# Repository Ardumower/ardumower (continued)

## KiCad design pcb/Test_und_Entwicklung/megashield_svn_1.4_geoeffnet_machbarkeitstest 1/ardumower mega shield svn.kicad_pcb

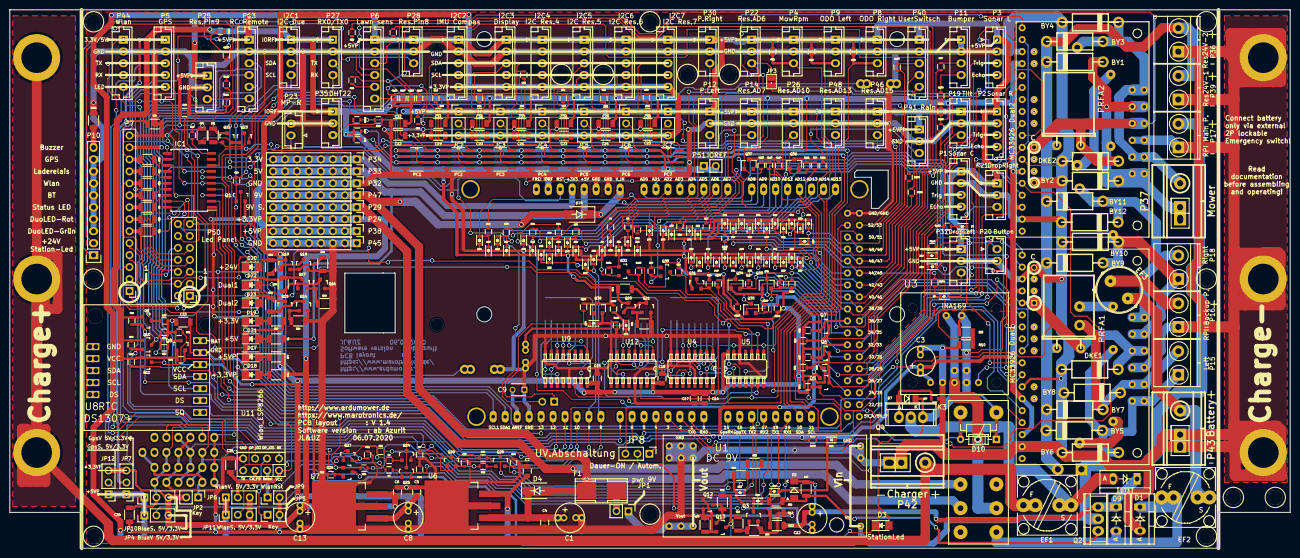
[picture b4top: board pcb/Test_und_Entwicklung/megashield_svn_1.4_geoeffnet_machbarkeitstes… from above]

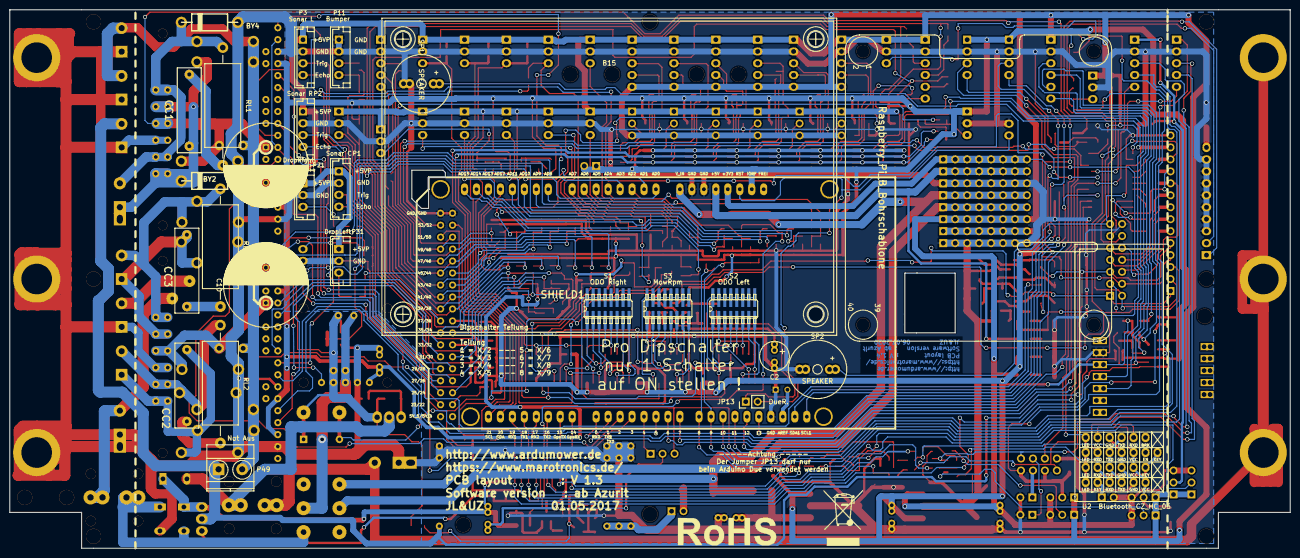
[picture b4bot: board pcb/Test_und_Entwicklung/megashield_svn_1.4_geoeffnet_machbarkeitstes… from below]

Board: 2 copper layers, 271.8 x 114.3 mm, 442 parts (21 on the bottom side), 281 nets.

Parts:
B1, B2, B3, B4, B5, B6, B7, B8, B17, B18, B19, B20, B21, B22: Bohrloch_3,2mm
B9, B10, B11, B12, B13, B14: Bohrloch_6,5mm
B15: BumperDuino_Bohrschablone
B16: Raspberry_Pi_B_Bohrschablone; Raspberry_Pi_B_Bohrschablone_Rueckseite
B23: Mülleimer; WEEE-Logo_8.4x12mm_SilkScreen
B24: Rohos; RoHS-Logo_6mm_SilkScreen
BY1, BY2, BY3, BY4, BY5, BY6, BY7, BY8, BY9, BY10, BY11, BY12: BY 500/1000; Diode_liegend_BY500_1000_RM15
C1, C8, C13: 22uF; Elko_vert_11.2x6.3mm_RM2.5_RM5.0
C2: 47uF; Elko_vert_11.2x6.3mm_RM2.5_RM5.0
C3: 10uF; Elko_vert_11.2x6.3mm_RM2.5_RM5.0
C4, C5, C6, C7, C14, C15, C16, C17, C18: 100nF; C_0805
C9: 100nF; C_Disc_D3_P2.5
C10, C11: 2200uF 63V; C_Radial_D18_L36_P7.5
C12: 22uF / 63V; Elko_vert_11.2x6.3mm_RM2.5_RM5.0
C19, C20, C21, C22, C23, C24, C25, C26, C27, C28, C29, C30, C31, C32, C33, C34, C35, C36: 100nF; C_1206
CC1, CC2, CC3: MP3-Y2 10N; Kondensator_cnp_18x5mm
D1, D9: MBR 1045; Diode_TO-220_Vertical
D2, D7: SMD ZF 15; MiniMELF_Standard
D3: StationLed; LED_1206
D4, D74: S 1G SMD; D_SMA_Standard
D5, D6, D8, D11, D12, D13, D14, D15, D16, D24, D25, D26, D27, D28, D29, D30, D31, D32, D33, D34, D35, D36, D37, D38, D39, D40, D41, D42, D43, D44, D45, D46, D47, D48, D49, D50, D51, D52, D53, D54, D55, D56, D57, D58, D59, D60, D61, D62, D63, D64, D65, D66, D67, D68, D69, D70, D71, D72, D75, D76: TSS0230LU; D_0603
D10: 1N4148; D_DO-35_SOD27_P7.62mm_Horizontal
D17: +5VP; LED_1206
D18: +3,3VP; LED_1206
D19: +3,3V; LED_1206
D20: +24V; LED_1206
D21: +5V; LED_1206
D22: Dual1; LED_1206
D23: Dual2; LED_1206
D73: MBR 1045; MBR1045
DKE1, DKE2: 15KE33CA; Diode_liegend_BY500_1000_RM15
Dual1, Dual2: MC33926; MC_33926_31polig_mit_Bohrloch_neue_Masse_mit_zweite_Lochrei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
EF1: F_5A; Fuseholder5x20_vert_closed_Bulgin_FX0456_und_TR15_Halter
EF2: F_10A; Fuseholder5x20_vert_closed_Bulgin_FX0456_und_TR15_Halter
EF3: 1A; Sicherungs_Sockel_für_TR5_TE5
F1: PTC; Fuse_SMD
I2C1: I2C Due; JST_EH_B04B-EH-A_04x2.50mm_Straight
I2C2: IMU Compas; JST_EH_B05B-EH-A_05x2.50mm_Straight
I2C3: Display; JST_EH_B05B-EH-A_05x2.50mm_Straight
I2C4: I2C Res.4; JST_EH_B05B-EH-A_05x2.50mm_Straight
I2C5: I2C Res.5; JST_EH_B05B-EH-A_05x2.50mm_Straight
I2C6: I2C Res.6; JST_EH_B05B-EH-A_05x2.50mm_Straight
I2C7: I2C Res.7; JST_EH_B05B-EH-A_05x2.50mm_Straight
IC1: UDN 2987 LWTR-6T; SOIC-20W_7.5x12.8mm_Pitch1.27mm
JC2, JC3, JC4, JC5, JC6, JC7: JUMPER3; Pin_Header_Straight_1x03_Pitch2.54mm
JP1: pwr 9V; Pin_Header_Straight_1x02_Pitch2.54mm
JP2, JP5: Key; Pin_Header_Straight_1x02_Pitch2.54mm
JP3: M1FB; SJ
JP4: BlueV 5V/3.3V; Pin_Header_Straight_1x03_Pitch2.54mm
JP6: WlanV. 5V/3.3V; Pin_Header_Straight_1x03_Pitch2.54mm
JP7: GpsV 5V/3.3V; Pin_Header_Straight_1x03_Pitch2.54mm
JP8: UV.Abschaltung; Pin_Header_Straight_1x03_Pitch2.54mm
JP9: WlanRst; Pin_Header_Straight_1x02_Pitch2.54mm
JP10: BlueS. 5V/3.3V; Pin_Header_Straight_1x03_Pitch2.54mm
JP11: WlanS. 5V/3.3V; Pin_Header_Straight_1x03_Pitch2.54mm
JP12: GpsS. 5V/3.3V; Pin_Header_Straight_1x03_Pitch2.54mm
JP13: DueR.; Pin_Header_Straight_1x02_Pitch2.54mm
K3: RELAY_2RT; Relais_DPDT_Schrack-RT2_RM5mm_3D_Kontaktbelegung_geändert_F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
P1: Sonar C; JST_EH_B04B-EH-A_04x2.50mm_Straight
P2: Sonar R; JST_EH_B04B-EH-A_04x2.50mm_Straight
P3: Sonar L; JST_EH_B04B-EH-A_04x2.50mm_Straight
P4: MowRpm; JST_EH_B03B-EH-A_03x2.50mm_Straight
P5: GPS; JST_EH_B05B-EH-A_05x2.50mm_Straight
P6: Lawn sens; JST_EH_B06B-EH-A_06x2.50mm_Straight
P7: Status LEDs; Socket_Strip_Straight_1x14_Pitch2.54mm
P8: ODO Right; JST_EH_B03B-EH-A_03x2.50mm_Straight
P9: ODO Left; JST_EH_B03B-EH-A_03x2.50mm_Straight
P10: Status LEDs GND; Socket_Strip_Straight_1x10_Led_Bargraph_Anzeige
P11: Bumper; JST_EH_B04B-EH-A_04x2.50mm_Straight
P12: P.Left; JST_EH_B03B-EH-A_03x2.50mm_Straight
P13: RC Remote; JST_EH_B06B-EH-A_06x2.50mm_Straight
P14: Res.AD7; JST_EH_B03B-EH-A_03x2.50mm_Straight
P15: Left; TerminalBlock_Pheonix_MKDS1.5-2pol
P16: RPI Backup P.; TerminalBlock_Pheonix_MKDS1.5-2pol
P17: RPI Main P.; TerminalBlock_Pheonix_MKDS1.5-2pol
P18: Right; TerminalBlock_Pheonix_MKDS1.5-2pol
P19: Tilt; JST_EH_B03B-EH-A_03x2.50mm_Straight
P20: Button; JST_EH_B02B-EH-A_02x2.50mm_Straight
P21: DropRight; JST_EH_B03B-EH-A_03x2.50mm_Straight
P22: Res.AD6; JST_EH_B03B-EH-A_03x2.50mm_Straight
P23: MP-R; JST_EH_B02B-EH-A_02x2.50mm_Straight
P24: +3.3VP; Pin_Header_Straight_1x08_Pitch2.54mm
P25: Res.Pin9; JST_EH_B03B-EH-A_03x2.50mm_Straight
P26: Res.AD10; JST_EH_B03B-EH-A_03x2.50mm_Straight
P27: RX0/TX0; JST_EH_B04B-EH-A_04x2.50mm_Straight
P28: Res.Pin8; JST_EH_B03B-EH-A_03x2.50mm_Straight
P29: 9V S.; Pin_Header_Straight_1x08_Pitch2.54mm
P30: P.Right; JST_EH_B03B-EH-A_03x2.50mm_Straight
P31: DropLeft; JST_EH_B03B-EH-A_03x2.50mm_Straight
P32, P45: GND; Pin_Header_Straight_1x08_Pitch2.54mm
P33: 5V; Pin_Header_Straight_1x08_Pitch2.54mm
P34: 3,3V; Pin_Header_Straight_1x08_Pitch2.54mm
P35: DHT22; JST_EH_B03B-EH-A_03x2.50mm_Straight
P36: Res24V-2; TerminalBlock_Pheonix_MKDS1.5-2pol
P37: Mower; Anschlussklemme_RM5,08-RM7,62
P38: +5VP; Pin_Header_Straight_1x08_Pitch2.54mm
P39: Res24V-1; TerminalBlock_Pheonix_MKDS1.5-2pol
P40: UserSwitsch; JST_EH_B05B-EH-A_05x2.50mm_Straight
P41: Rain; JST_EH_B03B-EH-A_03x2.50mm_Straight
P42: Charger; Anschlussklemme_RM5,08-RM7,62
P43: Battery; Anschlussklemme_RM5,08-RM7,62
P44: Wlan; JST_EH_B05B-EH-A_05x2.50mm_Straight
P46: Res.AD15; JST_EH_B03B-EH-A_03x2.50mm_Straight
P47: 9V; Pin_Header_Straight_1x08_Pitch2.54mm
P48: Res.AD13; JST_EH_B03B-EH-A_03x2.50mm_Straight
P49: Not Aus; TerminalBlock_Pheonix_MKDS1.5-2pol
P50: Led Panel; Pin_Header_Straight_2x07_Pitch2.54mm
P51: IOREF; Socket_Strip_Straight_1x02_Pitch2.54mm
PC1, PC2, PC3, PC4, PC5, PC6, PC7: PCA9517D; SOIC127P600X175-8N
PRFA1, PRFA2: PFRA 500; PRFA_500
Q1, Q24, Q25, Q26, Q27, Q28, Q29, Q38: BC847B; SOT-23
Q2, Q4: IRF9540N; TO-220
Q3, Q12, Q13, Q14, Q15, Q16, Q17, Q18, Q19, Q20, Q21, Q22, Q23: BC817; SOT-23
Q5, Q6, Q7, Q8, Q9, Q10, Q11, Q30, Q31, Q32, Q33, Q34, Q35, Q36, Q37: BSS138; SOT-23
R1, R2, R5, R17, R20, R21, R22, R25, R77, R134: 220R; R_1206
R3, R4, R26, R27, R29, R50, R54, R82, R83, R84, R85, R86, R87, R88, R89, R90, R103, R104, R105, R106, R107, R108, R109, R110, R111, R112: 300R; R_0603
R6, R7, R16, R28, R30, R31, R92, R93, R96: 4K7; R_0603
R8, R14, R15, R39, R42, R46, R49, R51, R52, R53, R55, R56, R58, R59, R60, R61, R62, R63, R64, R65, R66, R67, R68, R69, R70, R71, R91, R94, R95, R97, R98, R99, R100, R101, R102, R113, R114, R115, R116, R117, R118, R119, R120, R121, R122, R123, R124, R131, R132, R133, R137: 10K; R_0603
R9, R12: 100K 0,1%; R_1206
R10, R13: 10K 0,1%; R_1206
R11, R73, R79: 68R; R_1206
R18, R43: 2k2; R_0603
R19, R38, R72, R74, R76, R81: 8K2; R_1206
R23, R33, R78: 100R; R_1206
R24, R75, R80: 180R; R_1206
R32: 1K; R_1206
R34, R35: 10K; R_1206
R36: 30K; R_1206
R37: 100K; R_1206
R40, R41, R44, R45, R47, R48, R125, R126, R127, R128, R129, R130: XXXX; R_0603
R57: 100K; R_0603
R135: 56K; R_0603
R136: 1K; R_0603
RL1, RL2, RL3: 1,8R 2W METALL; Resistor_Horizontal_RM25mm-2W
S1: ODO Right; SW_DIP_x8_SMD
S2: ODO Left; SW_DIP_x8_SMD
S3: MowRpm; SW_DIP_x8_SMD
SHIELD1: ARDUINO_MEGA_SHIELD; ARDUINO_MEGA_SHIELD_DUO_3D
SP1, SP2: SPEAKER; Buzzer_12x9.5RM7.6_RM5.0
U1: DC 9V; DC_DC_DSN2596_mit_Bohrloch_doppelte_Lochreihe
U2: Bluetooth_CZ_HC_05; Bluetooth_Buchse_Platz_mit_Beschriftung_4_fach
U3: INA169
U4, U9, U12: 4017; 40xx-SO16
U5: 4081; 40xx-SO14
U6: LM2940CS-5.0; TO-263-3Lead
U7: LM3940IS-3.3; TO-263-3Lead
U8: DS1307+; Tiny_RTC_DS1307_geändert_mit_Bohrloch_4Lochreihen
U11: Wlan_ESP8266; Wlan_ESP8266_3D_mit_Pin_Beschreibung_ohne_Rahmen

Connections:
9Vgeschaltet: K3.3 (R1), P29.1, P29.2, P29.3, P29.4, P29.5, P29.6, P29.7, P29.8
+3.3VP: C6.1, C13.1, I2C2.5, I2C3.5, I2C4.5, I2C5.5, I2C6.5, I2C7.5, JC2.3, JC3.3, JC4.3, JC5.3, JC6.3, JC7.3, JP2.2, JP4.3, JP6.3, JP7.3, JP10.3, JP11.3, JP12.3, P24.1, P24.2, P24.3, P24.4, P24.5, P24.6, P24.7, P24.8, R78.1, U7.3 (OUT)
+3V3: P34.1, P34.2, P34.3, P34.4, P34.5, P34.6, P34.7, P34.8, R23.1, SHIELD1.3V3
+5V: P33.1, P33.2, P33.3, P33.4, P33.5, P33.6, P33.7, P33.8, R1.1, SHIELD1.5V
+5VP: C5.1, C7.1, C8.1, C14.1, C15.1, C16.1, C17.1, C18.1, C22.1, C33.1, I2C2.1, I2C3.1, I2C4.1, I2C5.1, I2C6.1, I2C7.1, IC1.11 (VS), JC2.1, JC3.1, JC4.1, JC5.1, JC6.1, JC7.1, JP4.1, JP6.1, JP7.1, JP10.1, JP11.1, JP12.1, P1.1, P2.1, P3.1, P4.1, P6.1, P8.1, P9.1, P12.1, P13.1, P14.1, P19.1, P21.1, P22.1, P25.1, P26.1, P28.1, P30.1, P31.1, P38.1, P38.2, P38.3, P38.4, P38.5, P38.6, P38.7, P38.8, P40.1, P41.1, P46.1, P48.1, PC1.8 (VCCB), R28.2, R30.2, R31.1, R43.1, R59.1, R61.1, R63.1, R65.1, R67.1, R69.1, R71.1, R77.1, R98.1, R100.1, R102.1, R116.1, R118.1, R120.1, R122.1, R124.1, U4.16 (VDD), U5.14 (Vdd), U6.3 (OUT), U7.1 (IN), U8.3 (VCC), U9.16 (VDD), U12.16 (VDD)
+9V: D4.2 (A), D74.2 (A), F1.2, K3.5 (C1), P47.1, P47.2, P47.3, P47.4, P47.5, P47.6, P47.7, P47.8
+24V: D20.2 (A), P7.5, P17.2, P49.1, P50.5, Q2.2 (D), U1.3 (VIN)
/+24V: BY1.1 (K), BY3.1 (K), BY5.1 (K), BY7.1 (K), BY9.1 (K), BY11.1 (K), P36.2, P39.2, P49.2, PRFA1.1, PRFA2.1
/Anschlußstecker/5V_IN: P19.3, Q37.3 (D), R124.2
/Anschlußstecker/5V_IN_1: P1.4, Q5.3 (D), R59.2
/Anschlußstecker/5V_IN_2: P2.4, Q6.3 (D), R61.2
/Anschlußstecker/5V_IN_3: P2.3, Q34.3 (D), R118.2
/Anschlußstecker/5V_IN_4: P41.3, Q36.3 (D), R122.2
/Anschlußstecker/5V_IN_5: P3.4, Q7.3 (D), R63.2
/Anschlußstecker/5V_IN_6: P3.3, Q33.3 (D), R116.2
/Anschlußstecker/5V_IN_7: P1.3, Q35.3 (D), R120.2
/Anschlußstecker/5V_IN_8: P13.6, Q11.3 (D), R71.2
/Anschlußstecker/5V_IN_9: P13.5, Q10.3 (D), R69.2
/Anschlußstecker/5V_IN_10: P13.4, Q9.3 (D), R67.2
/Anschlußstecker/5V_IN_11: P13.3, Q8.3 (D), R65.2
/Anschlußstecker/Ausgang1: Q32.3 (D), R102.2, U5.3
/Anschlußstecker/Ausgang2: Q31.3 (D), R100.2, U5.4
/Anschlußstecker/Ausgang3: Q30.3 (D), R98.2, U5.10
/Anschlußstecker/Eingang1: P8.3, R28.1, U4.14 (CP0), U5.1
/Anschlußstecker/Eingang2: P9.3, R30.1, U5.5, U9.14 (CP0)
/Anschlußstecker/Eingang3: P4.3, R31.2, U5.8, U12.14 (CP0)
/Batterieeingang 24V: C12.1, D2.1 (K), D9.1 (K), D73.1 (K), Q2.3 (S), R12.1, R37.1
/Eingang: D73.2 (A), EF1.2, Q4.2 (D)
/Motortreiber/MotorOUT1: BY9.2 (A), BY10.1 (K), CC3.1, Dual1.23 (M2OUT1), P18.1
/Motortreiber/MotorOUT1_1: BY5.2 (A), BY6.1 (K), CC2.1, Dual1.19 (M1OUT1), P15.1
/Motortreiber/MotorOUT1_2: BY1.2 (A), BY2.1 (K), CC1.1, Dual2.19 (M1OUT1), Dual2.23 (M2OUT1), P37.1
/Motortreiber/MotorOUT2: BY3.2 (A), BY4.1 (K), Dual2.20 (M1OUT2), Dual2.24 (M2OUT2), P37.2, RL1.2
/Motortreiber/MotorOUT2_1: BY7.2 (A), BY8.1 (K), Dual1.20 (M1OUT2), P15.2, RL2.2
/Motortreiber/MotorOUT2_2: BY11.2 (A), BY12.1 (K), Dual1.24 (M2OUT2), P18.2, RL3.2
Charg_Pin_+: B9.1 (B3,2), B10.1 (B3,2), B11.1 (B3,2), EF1.1, P42.2
DHT22: P35.3, R39.2, R109.1
DropLeft: D5.1 (K), P31.3
DropRight: D6.1 (K), P21.3
Dual1: C10.1, D22.2 (A), DKE1.1 (K), Dual1.22 (VIN), PRFA1.2
Dual2: C11.1, D23.2 (A), DKE2.1 (K), Dual2.22 (VIN), PRFA2.2
DuoLED-Rot: IC1.2 (IN2), SHIELD1.7
DuoLED_Grün: IC1.1 (IN1), SHIELD1.6
GND: B12.1 (B3,2), B13.1 (B3,2), B14.1 (B3,2), BY2.2 (A), BY4.2 (A), BY6.2 (A), BY8.2 (A), BY10.2 (A), BY12.2 (A), C1.2, C2.2, C3.2, C4.2, C5.2, C6.2, C7.2, C8.2, C9.1, C10.2, C11.2, C13.2, C14.2, C15.2, C16.2, C17.2, C18.2, C19.2, C20.2, C21.2, C22.2, C23.2, C24.2, C25.2, C26.2, C27.2, C28.2, C29.2, C30.2, C31.2, C32.2, C33.2, C34.2, C35.2, C36.2, D1.2 (A), D16.2 (A), D17.1 (K), D18.1 (K), D19.1 (K), D21.1 (K), D24.2 (A), D25.2 (A), D27.2 (A), D30.2 (A), D34.2 (A), D35.2 (A), D36.2 (A), D38.2 (A), D40.2 (A), D42.2 (A), D44.2 (A), D46.2 (A), D48.2 (A), D50.2 (A), D52.2 (A), D54.2 (A), D56.2 (A), D58.2 (A), D60.2 (A), D62.2 (A), D64.2 (A), D66.2 (A), D68.2 (A), D70.2 (A), D72.2 (A), D75.2 (A), DKE1.2 (A), DKE2.2 (A), Dual1.2 (GND), Dual1.7 (M1D1), Dual1.16 (M2D1), Dual1.21 (GND), Dual2.2 (GND), Dual2.7 (M1D1), Dual2.16 (M2D1), Dual2.21 (GND), I2C1.2, I2C2.2, I2C3.2, I2C4.2, I2C5.2, I2C6.2, I2C7.2, IC1.12 (GND), JP5.2, JP9.2, P1.2, P2.2, P3.2, P4.2, P5.2, P6.2, P7.14, P8.2, P9.2, P10.3, P10.4, P10.5, P10.6, P10.7, P10.8, P10.9, P11.1, P11.2, P12.2, P13.2, P14.2, P16.1, P17.1, P19.2, P20.2, P21.2, P22.2, P23.2, P25.2, P26.2, P27.2, P28.2, P30.2, P31.2, P32.1, P32.2, P32.3, P32.4, P32.5, P32.6, P32.7, P32.8, P35.2, P36.1, P39.1, P40.2, P41.2, P42.1, P43.1, P44.2, P45.1, P45.2, P45.3, P45.4, P45.5, P45.6, P45.7, P45.8, P46.2, P48.2, P50.14, PC1.4 (GND), PC2.4 (GND), PC3.4 (GND), PC4.4 (GND), PC5.4 (GND), PC6.4 (GND), PC7.4 (GND), Q1.2 (E), Q3.2 (E), Q12.2 (E), Q14.2 (E), Q16.2 (E), Q18.2 (E), Q21.2 (E), Q23.2 (E), R8.2, R10.2, R11.2, R13.2, R14.2, R15.2, R24.2, R35.2, R57.2, R73.2, R75.2, R79.2, R80.2, R91.2, R94.2, R95.2, R134.2, R136.2, SHIELD1.GND1, SHIELD1.GND2, SHIELD1.GND3, SHIELD1.GND4, SHIELD1.GND5, SP1.1, SP2.1, U1.1 (GND), U1.4 (GND), U2.GND, U3.2 (GND), U4.8 (VSS), U4.13 (~CP1), U5.7 (Vss), U5.12, U5.13, U6.2 (GND_2), U6.4 (GND), U7.2 (GND_2), U7.4 (GND), U8.2 (GND), U9.8 (VSS), U9.13 (~CP1), U11.GND, U12.8 (VSS), U12.13 (~CP1)
GPS-LED: IC1.7 (IN7), P5.5
GPS_RX: Q28.2 (E), R94.1, SHIELD1.15 (RX3)
GPS_TX: R96.2, SHIELD1.14 (TX3)
IOREF: C3.1, C26.1, C27.1, C28.1, C29.1, C30.1, C31.1, C32.1, D8.1 (K), D11.1 (K), D26.1 (K), D28.1 (K), D29.1 (K), D31.1 (K), D32.1 (K), D33.1 (K), D37.1 (K), D39.1 (K), D41.1 (K), D43.1 (K), D45.1 (K), D47.1 (K), D49.1 (K), D51.1 (K), D53.1 (K), D55.1 (K), D57.1 (K), D59.1 (K), D61.1 (K), D63.1 (K), D65.1 (K), D67.1 (K), D69.1 (K), D71.1 (K), Dual1.3 (Vdd), Dual1.6 (M1nD2), Dual1.15 (M2nD2), Dual2.3 (Vdd), Dual2.6 (M1nD2), Dual2.15 (M2nD2), I2C1.1, JP8.3, P27.1, P35.1, P51.1, P51.2, PC1.1 (VCCA), PC2.1 (VCCA), PC3.1 (VCCA), PC4.1 (VCCA), PC5.1 (VCCA), PC6.1 (VCCA), PC7.1 (VCCA), Q5.1 (G), Q6.1 (G), Q7.1 (G), Q8.1 (G), Q9.1 (G), Q10.1 (G), Q11.1 (G), Q24.3 (C), Q25.3 (C), Q28.3 (C), Q30.1 (G), Q31.1 (G), Q32.1 (G), Q33.1 (G), Q34.1 (G), Q35.1 (G), Q36.1 (G), Q37.1 (G), Q38.3 (C), R39.1, R47.1, R48.1, R58.1, R60.1, R62.1, R64.1, R66.1, R68.1, R70.1, R97.1, R99.1, R101.1, R113.2, R114.2, R115.1, R117.1, R119.1, R121.1, R123.1, R125.2, R126.2, R127.2, R128.2, R129.2, R130.2, R131.2, R132.2, R133.2, R135.1, R137.2, SHIELD1.IORE (IOREF), U3.1 (VCC)
Led-BT: IC1.4 (IN4), U2.LED
Led-Status: IC1.3 (IN3), SHIELD1.13
Led-Wlan: IC1.5 (IN5), P44.5, U11.GP_2 (GP_IO2)
unnamed: C1.1, C4.1, D4.1 (K), U6.1 (IN)
unnamed: C2.1, D75.1 (K), Q38.1 (B), R135.2
unnamed: C9.2, SHIELD1.AREF
unnamed: C12.2, D12.2 (A), R34.1
unnamed: C19.1, JC2.2, PC2.8 (VCCB), R40.1, R44.1
unnamed: C20.1, JC3.2, PC3.8 (VCCB), R41.1, R45.1
unnamed: C21.1, JC4.2, PC4.8 (VCCB), R42.1, R46.1
unnamed: C23.1, JC5.2, PC5.8 (VCCB), R51.1, R55.1
unnamed: C24.1, JC6.2, PC6.8 (VCCB), R52.1, R56.1
unnamed: C25.1, JC7.2, PC7.8 (VCCB), R49.1, R53.1
unnamed: C34.1, JP4.2, U2.VCC
unnamed: C35.1, JP6.2, P44.1, U11.CH_P (CH_PD), U11.VCC
unnamed: C36.1, JP7.2, P5.1
unnamed: CC1.2, RL1.1
unnamed: CC2.2, RL2.1
unnamed: CC3.2, RL3.1
unnamed: D1.1 (K), D9.2 (A), EF2.1, K3.16 (T2)
unnamed: D2.2 (A), Q2.1 (G), R32.2, R37.2
unnamed: D3.1 (K), Q13.3 (C), R72.1
unnamed: D5.2 (A), R104.1
unnamed: D6.2 (A), R103.1
unnamed: D7.2 (A), Q4.1 (G), R57.1
unnamed: D10.2 (A), K3.9, Q1.3 (C)
unnamed: D11.2 (A), D24.1 (K), R3.2, SHIELD1.AD5
unnamed: D12.1 (K), R33.1, R34.2
unnamed: D13.2 (A), D15.2 (A), R32.1, R33.2
unnamed: D15.1 (K), Q3.3 (C)
unnamed: D8.2 (A), D16.1 (K), R4.2, SHIELD1.AD4
unnamed: D17.2 (A), R77.2
unnamed: D18.2 (A), R78.2
unnamed: D19.2 (A), R23.2
unnamed: D20.1 (K), Q19.3 (C), R76.1
unnamed: D21.2 (A), R1.2
unnamed: D22.1 (K), Q17.3 (C), R38.1
unnamed: D23.1 (K), Q15.3 (C), R19.1
unnamed: D25.1 (K), D26.2 (A), R103.2, R114.1, SHIELD1.23 (PA1)
unnamed: D27.1 (K), D28.2 (A), R110.2, SHIELD1.35 (PC2)
unnamed: D29.2 (A), D30.1 (K), R87.2, R132.1, SHIELD1.38 (PD7)
unnamed: D31.2 (A), D34.1 (K), R105.2, R131.1, SHIELD1.39 (PG2)
unnamed: D32.2 (A), D35.1 (K), R111.2, R129.1, SHIELD1.9
unnamed: D33.2 (A), D36.1 (K), R112.2, R130.1, SHIELD1.8
unnamed: D37.2 (A), D38.1 (K), R29.2, R126.1, SHIELD1.40 (PG1)
unnamed: D39.2 (A), D40.1 (K), R54.2, R125.1, SHIELD1.41 (PG0)
unnamed: D41.2 (A), D42.1 (K), R83.2, R128.1, SHIELD1.42 (PL7)
unnamed: D43.2 (A), D44.1 (K), R85.2, R127.1, SHIELD1.43 (PL6)
unnamed: D45.2 (A), D46.1 (K), R86.2, SHIELD1.44 (PL5)
unnamed: D47.2 (A), D48.1 (K), R104.2, R113.1, SHIELD1.45 (PL4)
unnamed: D49.2 (A), D50.1 (K), R108.2, SHIELD1.47 (PL2)
unnamed: D51.2 (A), D52.1 (K), R106.2, SHIELD1.46 (PL3)
unnamed: D53.2 (A), D54.1 (K), R26.2, SHIELD1.AD7
unnamed: D55.2 (A), D56.1 (K), R82.2, SHIELD1.AD6
unnamed: D57.2 (A), D58.1 (K), R109.2, SHIELD1.49 (PL0)
unnamed: D59.2 (A), D60.1 (K), R84.2, SHIELD1.AD2
unnamed: D61.2 (A), D62.1 (K), R107.2, SHIELD1.48 (PL1)
unnamed: D63.2 (A), D64.1 (K), R90.2, SHIELD1.AD8
unnamed: D65.2 (A), D66.1 (K), R27.2, SHIELD1.AD15
unnamed: D67.2 (A), D68.1 (K), R89.2, SHIELD1.AD9
unnamed: D69.2 (A), D70.1 (K), R50.2, SHIELD1.AD13
unnamed: D71.2 (A), D72.1 (K), R88.2, SHIELD1.AD10
unnamed: D74.1 (K), SHIELD1.V_IN
unnamed: D76.1 (K), Q38.2 (E), R136.1
unnamed: D76.2 (A), JP13.1, R137.1
unnamed: Dual2.9 (M1FB), JP3.2
unnamed: EF2.2, EF3.1, P43.2
unnamed: EF3.2, P16.2
unnamed: F1.1, JP1.2
unnamed: IC1.10 (OE/~R), R43.2
unnamed: IC1.13 (OUT8), P7.13, P50.13, SP1.2, SP2.2
unnamed: IC1.14 (OUT7), R25.1
unnamed: IC1.15 (OUT6), R17.1
unnamed: IC1.16 (OUT5), R22.1
unnamed: IC1.17 (OUT4), R2.1
unnamed: IC1.18 (OUT3), R5.1
unnamed: IC1.19 (OUT2), R20.1
unnamed: IC1.20 (OUT1), R21.1
unnamed: JP1.1, U1.2 (Vout)
unnamed: JP2.1, U2.Key
unnamed: JP5.1, U11.GP_0 (GP_IO0)
unnamed: JP8.2, R36.2
unnamed: JP9.1, U11.Rese (Reset)
unnamed: JP10.2, Q26.3 (C)
unnamed: JP11.2, Q27.3 (C)
unnamed: JP12.2, Q29.3 (C)
unnamed: K3.12 (C2), U3.5 (IP-)
unnamed: P5.3, R93.2
unnamed: P5.4, Q29.2 (E), R95.1
unnamed: P7.2, P10.1, P50.2, Q22.3 (C), R81.1
unnamed: P7.3, P10.2, P50.3, Q20.3 (C), R74.1
unnamed: P10.10, R134.1
unnamed: P44.3, R7.2, U11.TX
unnamed: P44.4, Q27.2 (E), R91.1, U11.RX
unnamed: P7.6, P50.6, R21.2
unnamed: P7.7, P50.7, R20.2
unnamed: P7.8, P50.8, R5.2
unnamed: P7.9, P50.9, R2.2
unnamed: P7.10, P50.10, R22.2
unnamed: P7.11, P50.11, R17.2
unnamed: P7.12, P50.12, R25.2
unnamed: Q1.1 (B), R18.2
unnamed: Q3.1 (B), R35.1, R36.1
unnamed: Q12.1 (B), Q13.2 (E), R73.1
unnamed: Q12.3 (C), Q13.1 (B), R72.2
unnamed: Q14.1 (B), Q15.2 (E), R24.1
unnamed: Q14.3 (C), Q15.1 (B), R19.2
unnamed: Q16.1 (B), Q17.2 (E), R75.1
unnamed: Q16.3 (C), Q17.1 (B), R38.2
unnamed: Q18.1 (B), Q19.2 (E), R80.1
unnamed: Q18.3 (C), Q19.1 (B), R76.2
unnamed: Q20.1 (B), Q21.3 (C), R74.2
unnamed: Q20.2 (E), Q21.1 (B), R11.1
unnamed: Q22.1 (B), Q23.3 (C), R81.2
unnamed: Q22.2 (E), Q23.1 (B), R79.1
unnamed: Q24.1 (B), R6.1
unnamed: Q25.1 (B), R7.1
unnamed: Q26.1 (B), R16.1
unnamed: Q26.2 (E), R15.1, U2.RXD
unnamed: Q27.1 (B), R92.1
unnamed: Q28.1 (B), R93.1
unnamed: Q29.1 (B), R96.1
unnamed: R6.2, U2.TXD
unnamed: S1.1, U4.4 (Q2)
unnamed: S1.2, U4.7 (Q3)
unnamed: S1.3, U4.10 (Q4)
unnamed: S1.4, U4.1 (Q5)
unnamed: S1.5, U4.5 (Q6)
unnamed: S1.6, U4.6 (Q7)
unnamed: S1.7, U4.9 (Q8)
unnamed: S1.8, U4.11 (Q9)
unnamed: S1.9, S1.10, S1.11, S1.12, S1.13, S1.14, S1.15, S1.16, U4.15 (MR)
unnamed: S2.1, U9.4 (Q2)
unnamed: S2.2, U9.7 (Q3)
unnamed: S2.3, U9.10 (Q4)
unnamed: S2.4, U9.1 (Q5)
unnamed: S2.5, U9.5 (Q6)
unnamed: S2.6, U9.6 (Q7)
unnamed: S2.7, U9.9 (Q8)
unnamed: S2.8, U9.11 (Q9)
unnamed: S2.9, S2.10, S2.11, S2.12, S2.13, S2.14, S2.15, S2.16, U9.15 (MR)
unnamed: S3.1, U12.4 (Q2)
unnamed: S3.2, U12.7 (Q3)
unnamed: S3.3, U12.10 (Q4)
unnamed: S3.4, U12.1 (Q5)
unnamed: S3.5, U12.5 (Q6)
unnamed: S3.6, U12.6 (Q7)
unnamed: S3.7, U12.9 (Q8)
unnamed: S3.8, U12.11 (Q9)
unnamed: S3.9, S3.10, S3.11, S3.12, S3.13, S3.14, S3.15, S3.16, U12.15 (MR)
unnamed: U4.2 (Q1), U5.2
unnamed: U5.6, U9.2 (Q1)
unnamed: U5.9, U12.2 (Q1)
RX0: P27.3, SHIELD1.0 (RX0)
RX1: Q25.2 (E), R14.1, SHIELD1.19 (RX1)
RX2: Q24.2 (E), R8.1, SHIELD1.17 (RX2)
RelaisAbschaltung: JP8.1, SHIELD1.4
ReserveAD6: JP3.1, P22.3, R82.1
ReserveAD7: P14.3, R26.1
ReserveAD10: P26.3, R88.1
ReservePin8: P28.3, R112.1
ReservePin9: P25.3, R111.1
Reset: JP13.2, P23.1, SHIELD1.RST
Resv.PinAD13: P48.3, R50.1
Resv.PinAD15: P46.3, R27.1
SCL: PC1.2 (SCLA), PC2.2 (SCLA), PC3.2 (SCLA), PC4.2 (SCLA), PC5.2 (SCLA), PC6.2 (SCLA), PC7.2 (SCLA), R48.2, SHIELD1.21 (SCL)
SCL1: PC1.7 (SCLB), U8.5 (SCL)
SCL2: I2C2.4, PC2.7 (SCLB), R44.2
SCL3: I2C3.4, PC3.7 (SCLB), R45.2
SCL4: I2C4.4, PC4.7 (SCLB), R46.2
SCL5: I2C5.4, PC5.7 (SCLB), R51.2
SCL6: I2C6.4, PC6.7 (SCLB), R52.2
SCL7: I2C7.4, PC7.7 (SCLB), R49.2
SCL22: I2C1.4, SHIELD1.SCL1
SDA: PC1.3 (SDAA), PC2.3 (SDAA), PC3.3 (SDAA), PC4.3 (SDAA), PC5.3 (SDAA), PC6.3 (SDAA), PC7.3 (SDAA), R47.2, SHIELD1.20 (SDA)
SDA1: PC1.6 (SDAB), U8.4 (SDA)
SDA2: I2C2.3, PC2.6 (SDAB), R40.2
SDA3: I2C3.3, PC3.6 (SDAB), R41.2
SDA4: I2C4.3, PC4.6 (SDAB), R42.2
SDA5: I2C5.3, PC5.6 (SDAB), R55.2
SDA6: I2C6.3, PC6.6 (SDAB), R56.2
SDA7: I2C7.3, PC7.6 (SDAB), R53.2
SDA22: I2C1.3, SHIELD1.SDA1
StationLed: D3.2 (A), D7.1 (K), D10.1 (K), K3.8, P7.4, P50.4, Q4.3 (S), R9.1, U3.4 (IP+)
TX0: P27.4, SHIELD1.1 (TX0)
TX1: R92.2, SHIELD1.18 (TX1)
TX2: R16.2, SHIELD1.16 (TX2)
Taster: D13.1 (K), D14.1 (K), P7.1, P20.1, P50.1
pinBatteryVoltage: R12.2, R13.1, R84.1
pinBumperLeft: P11.4, R105.1
pinBumperRight: P11.3, R87.1
pinButton: D14.2 (A), R133.1, SHIELD1.51 (PB2_(MOSI))
pinBuzzer: IC1.8 (IN8), SHIELD1.53 (PB0_(SS))
pinChargeCurrent: R90.1, U3.3 (OUT)
pinChargeVoltage: R9.2, R10.1, R89.1
pinChargingEnable: IC1.6 (IN6), R18.1, SHIELD1.50 (PB3_(MISO))
pinLawnBackRecv: P6.6, R83.1
pinLawnBackSend: P6.5, R85.1
pinLawnFrontRecv: P6.4, R29.1
pinLawnFrontSend: P6.3, R54.1
pinMotorEnable: Dual1.10 (EN), SHIELD1.37 (PC0)
pinMotorLeftDir: Dual1.4 (M1IN2), SHIELD1.31 (PC6)
pinMotorLeftFault: Dual1.8 (M1nSF), SHIELD1.25 (PA3)
pinMotorLeftPWM: Dual1.5 (M1IN1), SHIELD1.5
pinMotorLeftSense: Dual1.9 (M1FB), SHIELD1.AD1
pinMotorMowDir: Dual2.4 (M1IN2), Dual2.13 (M2IN2), SHIELD1.29 (PA7)
pinMotorMowEnable: Dual2.10 (EN), SHIELD1.28 (PA6)
pinMotorMowFault: Dual2.8 (M1nSF), Dual2.17 (M2nSF), SHIELD1.26 (PA4)
pinMotorMowPWM: Dual2.5 (M1IN1), Dual2.14 (M2IN1), SHIELD1.2
pinMotorMowRpm_neu: Q30.2 (S), R97.2, SHIELD1.AD11
pinMotorMowSense: Dual2.18 (M2_FB), SHIELD1.AD3
pinMotorRightDir: Dual1.13 (M2IN2), SHIELD1.33 (PC4)
pinMotorRightFault: Dual1.17 (M2nSF), SHIELD1.27 (PA5)
pinMotorRightPWM: Dual1.14 (M2IN1), SHIELD1.3
pinMotorRightSense: Dual1.18 (M2_FB), SHIELD1.AD0
pinOdometryLeft: Q31.2 (S), R99.2, SHIELD1.AD12
pinOdometryRight: Q32.2 (S), R101.2, SHIELD1.AD14
pinPerimeterLeft: P12.3, R3.1
pinPerimeterRight: P30.3, R4.1
pinRain: Q36.2 (S), R86.1, R121.2
pinRemoteMow: Q8.2 (S), R64.2, SHIELD1.12
pinRemoteSpeed: Q10.2 (S), R68.2, SHIELD1.10
pinRemoteSteer: Q9.2 (S), R66.2, SHIELD1.11
pinRemoteSwitch: Q11.2 (S), R70.2, SHIELD1.52 (PB1_(SCK))
pinSonarCenterEcho: Q5.2 (S), R58.2, SHIELD1.22 (PA0)
pinSonarCenterTrigger: Q35.2 (S), R119.2, SHIELD1.24 (PA2)
pinSonarLeftEcho: Q7.2 (S), R62.2, SHIELD1.36 (PC1)
pinSonarLeftTrigger: Q33.2 (S), R115.2, SHIELD1.34 (PC3)
pinSonarRightEcho: Q6.2 (S), R60.2, SHIELD1.32 (PC5)
pinSonarRightTrigger: Q34.2 (S), R117.2, SHIELD1.30 (PC7)
pinTilt: Q37.2 (S), R110.1, R123.2
pinUserSwitch1: P40.5, R106.1
pinUserSwitch2: P40.4, R108.1
pinUserSwitch3: P40.3, R107.1

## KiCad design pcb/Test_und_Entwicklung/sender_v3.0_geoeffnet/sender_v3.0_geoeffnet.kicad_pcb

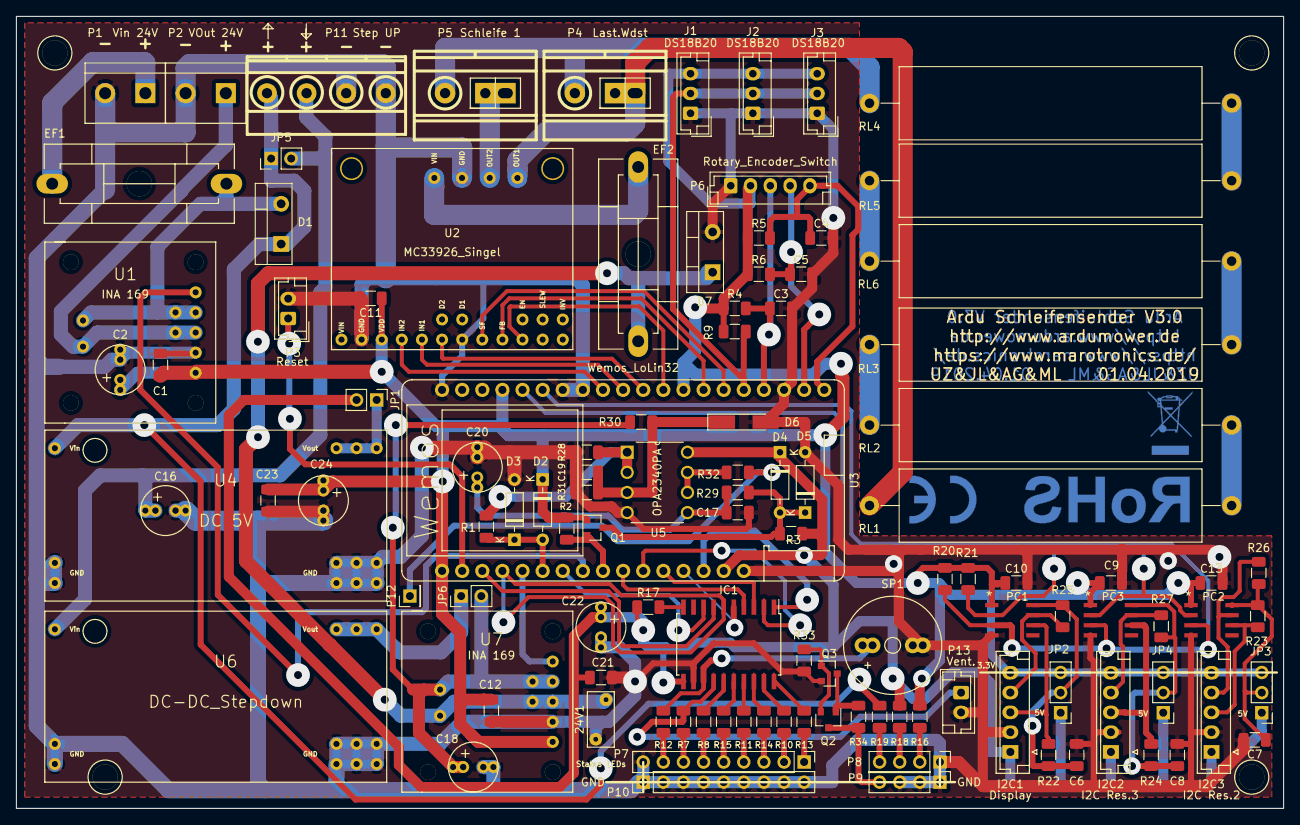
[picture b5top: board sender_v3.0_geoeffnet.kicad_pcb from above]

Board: 2 copper layers, 160.0 x 100.0 mm, 116 parts (0 on the bottom side), 84 nets.

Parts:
24V1: VR; RV_Disc_D7mm_W3.4mm_P5mm
B1, B2, B3, B4: Bohrloch_3,2mm
C1, C6, C7, C8, C9, C10, C11, C12, C13, C21, C23: 100nF; C_1206_3216Metric
C2: 10uF; Elko_vert_11.2x6.3mm_RM2.5_RM5.0
C3, C4, C5: 10nF; C_1206_3216Metric
C16, C18: 220uF/63V; Elko_vert_11.2x6.3mm_RM2.5_RM5.0
C17: 220nF; C_1206_3216Metric
C19: 47pP; C_1206_3216Metric
C20: 47uF/16V; Elko_vert_11.2x6.3mm_RM2.5_RM5.0
C22, C24: 10uF/16V; Elko_vert_11.2x6.3mm_RM2.5_RM5.0
D1, D7: MBR 1045; TO-220-2_Vertical
D2, D3, D4, D5: 1N4148; D_DO-35_SOD27_P7.62mm_Horizontal
D6: ZPD5,1V; D_MiniMELF_Handsoldering
EF1: F_5A; Fuseholder_Reichelt_PL112000
EF2: ????; Fuseholder_Reichelt_PL112000
I2C1: Display; JST_EH_B05B-EH-A_05x2.50mm_Straight
I2C2: I2C Res.3; JST_EH_B05B-EH-A_05x2.50mm_Straight
I2C3: I2C Res.2; JST_EH_B05B-EH-A_05x2.50mm_Straight
IC1: UDN 2987 LWTR-6T; SOIC-20W_7.5x12.8mm_P1.27mm
J1, J2, J3: DS18B20; JST_EH_B3B-EH-A_1x03_P2.50mm_Vertical
JP1: pwr 5V; PinHeader_1x02_P2.54mm_Vertical
JP2, JP3, JP4: Jumper_NC_Dual; PinHeader_1x03_P2.54mm_Vertical
JP5: Jumper_NC_Small; PinHeader_1x02_P2.54mm_Vertical
JP6: PWR; PinHeader_1x02_P2.54mm_Vertical
P1: Vin 24V; Anschlussklemme_2P_RM5,08
P2: VOut 24V; Anschlussklemme_2P_RM5,08
P3: Reset; JST_EH_B2B-EH-A_1x02_P2.50mm_Vertical
P4: Last.Wdst; Anschlussklemme_RM5,08-RM7,62
P5: Schleife 1; Anschlussklemme_RM5,08-RM7,62
P6: Rotary_Encoder_Switch; JST_EH_B5B-EH-A_1x05_P2.50mm_Vertical
P7: Status LEDs; PinHeader_1x09_P2.54mm_Vertical
P8: Spannungs Led; PinHeader_1x04_P2.54mm_Vertical
P9: Spannungs Led GND; PinHeader_1x04_P2.54mm_Vertical
P10: Status LEDs GND; PinHeader_1x09_P2.54mm_Vertical
P11: Step UP; mkds_1,5-4
P12: U5; PinHeader_1x01_P2.54mm_Vertical
P13: Vent.; JST_EH_B2B-EH-A_1x02_P2.50mm_Vertical
PC1, PC2, PC3: PCA9517D; SOIC127P600X175-8N
Q1: BSS138; SOT-23
Q2, Q3: BC817; SOT-23
R1: 300; R_1206_3216Metric
R2, R3, R5, R6, R24, R27: 10K; R_1206_3216Metric
R4, R20, R21, R22, R23, R25, R26: XXXX; R_1206_3216Metric
R7, R19: 0R; R_1206_3216Metric
R8, R10, R11, R12, R13, R14, R15, R18: 220R; R_1206_3216Metric
R9: 4K7; R_1206_3216Metric
R16: 100R; R_1206_3216Metric
R17: 2k2; R_1206_3216Metric
R28, R31: 10K/1%; R_1206_3216Metric
R29: 47K; R_1206_3216Metric
R30: 100K/1%; R_1206_3216Metric
R32: 1K; R_1206_3216Metric
R33: 68R; R_1206_3216Metric
R34: 8K2; R_1206_3216Metric
RL1, RL2, RL3: 2,2R 9W; R_Axial_Power_L38.0mm_W9.0mm_P45.72mm
RL4, RL5, RL6: 1,8R 9W; R_Axial_Power_L38.0mm_W9.0mm_P45.72mm
SP1: SPEAKER; Buzzer_12x9.5RM7.6_RM5.0
U1, U7: INA 169; INA169
U2: MC33926_Singel
U3: Wemos_LoLin32; LoLin_32_Board
U4: DC 5V; DC_DC_DSN2596_mit_Bohrloch_doppelte_Lochreihe
U5: OPA2340PA; opa2340
U6: DC-DC_Stepdown; DC_DC_DSN2596_mit_Bohrloch_doppelte_Lochreihe

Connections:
16V_geregelt: EF2.1, U2.13
+3V3: C1.1, C2.1, C9.1, C10.1, C11.1, C12.1, C13.1, C23.1, C24.1, D2.1, I2C1.5, I2C2.5, I2C3.5, J1.3, J2.3, J3.3, JP2.3, JP3.3, JP4.3, P6.2, PC1.1, PC2.1, PC3.1, Q1.1, R2.1, R4.1, R5.1, R6.1, R9.1, R16.1, R20.1, R21.1, U1.1, U2.3, U3.1, U3.20, U3.29, U7.1
+5V: C21.1, C22.1, D4.1, I2C1.1, I2C2.1, I2C3.1, IC1.11, JP1.2, JP2.1, JP3.1, JP4.1, R3.1, R17.1, R18.1, U3.15, U5.8
+24V: D1.1, JP5.1, P11.4, R19.1, U4.3
D2 pwm: U2.6, U3.27
DC_Wandler_Pin_4: P12.1, R32.1
EN: U2.10, U3.28
EncoderA: C4.1, P6.5, R5.2, U3.36
EncoderB: C5.1, P6.4, R6.2, U3.35
FB: U2.9, U3.30
GND: 24V1.2, C1.2, C2.2, C3.2, C4.2, C5.2, C6.2, C7.2, C8.2, C9.2, C10.2, C11.2, C12.2, C13.2, C16.2, C17.2, C18.2, C19.2, C20.2, C21.2, C22.2, C23.2, C24.2, D3.2, D5.2, D6.2, D7.2, I2C1.2, I2C2.2, I2C3.2, IC1.12, J1.1, J2.1, J3.1, P1.2, P2.2, P3.2, P6.1, P7.9, P8.1, P9.1, P9.2, P9.3, P10.1, P10.2, P10.3, P10.4, P10.5, P10.6, P10.7, P10.8, P10.9, P11.1, P11.2, P13.2, PC1.4, PC2.4, PC3.4, Q3.2, R28.2, R31.2, R33.2, SP1.1, U1.2, U2.2, U2.7, U2.14, U3.16, U3.17, U3.23, U3.24, U3.34, U4.1, U4.4, U5.4, U6.1, U6.4, U7.2
IN1: U2.5, U3.26
IN2: U2.4, U3.25
LED_Motortreiber_ÜLast+Temp_Rot: IC1.5, U3.13
LED_SchleifenStatus_Gelb: IC1.3, U3.12
LED_SchleifenStatus_Grün: IC1.2, U3.11
LED_SchleifenStatus_Rot: IC1.4, U3.10
Ladestrom: U1.3, U3.8
LevelS.: Q1.2, R2.2, U3.9
Mover_in_Ladestation: IC1.1, U3.14
unnamed: 24V1.1, D7.1, EF2.2, U7.5
unnamed: C6.1, JP2.2, PC1.8, R22.1, R25.1
unnamed: C7.1, JP3.2, PC2.8, R23.1, R26.1
unnamed: C8.1, JP4.2, PC3.8, R24.1, R27.1
unnamed: C16.1, JP5.2, P11.3, U6.3
unnamed: C17.1, C20.1, R29.1, U5.5
unnamed: C18.1, JP6.2, R30.1, U7.4
unnamed: C19.1, D6.1, R30.2, R31.1, U5.3
unnamed: D1.2, EF1.1, U1.4
unnamed: D2.2, D3.1, R1.2, U3.6
unnamed: EF1.2, P1.1
unnamed: IC1.10, R17.2
unnamed: IC1.13, R12.1, SP1.2
unnamed: IC1.14, P13.1, R7.1
unnamed: IC1.15, R8.1
unnamed: IC1.16, R15.1
unnamed: IC1.17, R11.1
unnamed: IC1.18, R14.1
unnamed: IC1.19, R10.1
unnamed: IC1.20, R13.1
unnamed: JP1.1, U4.2
unnamed: JP6.1, U6.2
unnamed: P2.1, U1.5
unnamed: P4.1, RL1.2, U2.16
unnamed: P4.2, P5.2, RL4.2
unnamed: P5.1, U2.15
unnamed: P7.1, R13.2
unnamed: P7.2, R10.2
unnamed: P7.3, R14.2
unnamed: P7.4, R11.2
unnamed: P7.5, R15.2
unnamed: P7.6, R8.2
unnamed: P7.7, R7.2
unnamed: P7.8, R12.2
unnamed: P8.2, R16.2
unnamed: P8.3, R18.2
unnamed: P8.4, R19.2
unnamed: P9.4, Q2.3, R34.1
unnamed: Q2.1, Q3.3, R34.2
unnamed: Q2.2, Q3.1, R33.1
unnamed: R32.2, U5.6, U5.7
unnamed: RL1.1, RL2.2
unnamed: RL2.1, RL3.2
unnamed: RL3.1, RL6.1
unnamed: RL4.1, RL5.2
unnamed: RL5.1, RL6.2
Pin36: IC1.7, U3.3
Pin39: IC1.6, U3.4
Reset: P3.1, U3.2
SCL: PC1.2, PC2.2, PC3.2, R21.2, U3.21
SCL2: I2C1.4, PC1.7, R25.2
SCL3: I2C3.4, PC2.7, R26.2
SCL4: I2C2.4, PC3.7, R27.2
SDA: PC1.3, PC2.3, PC3.3, R20.2, U3.22
SDA2: I2C1.3, PC1.6, R22.2
SDA3: I2C3.3, PC2.6, R23.2
SDA4: I2C2.3, PC3.6, R24.2
SF: U2.8, U3.31
SpannungLeistungsregelung: R1.1, R28.1, U5.1, U5.2
Steuer_Pin_Leistungsregelung: D4.2, D5.1, Q1.3, R3.2, R29.2
StromLeistungsregelung: U3.5, U7.3
Summer: IC1.8, U3.7
Taster: C3.1, P6.3, R4.2, U3.33
TempSensor: J1.2, J2.2, J3.2, R9.2, U3.32
